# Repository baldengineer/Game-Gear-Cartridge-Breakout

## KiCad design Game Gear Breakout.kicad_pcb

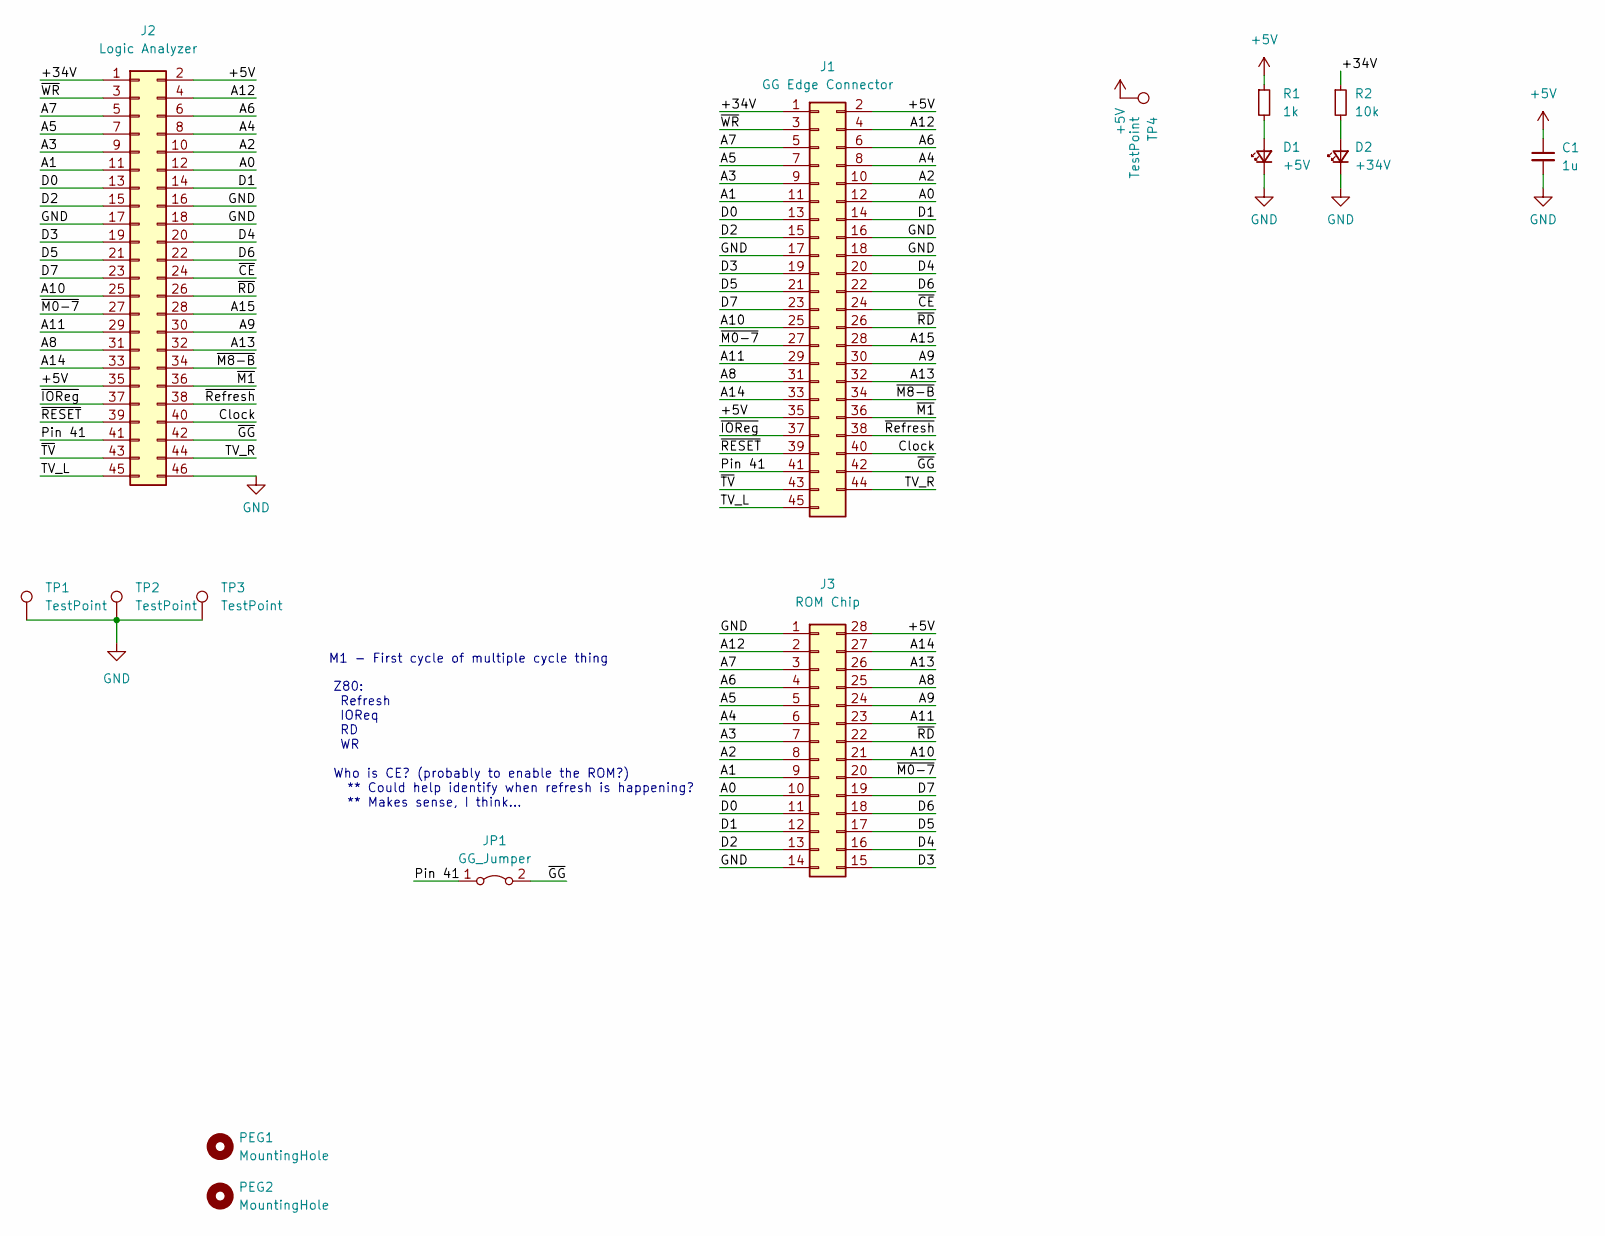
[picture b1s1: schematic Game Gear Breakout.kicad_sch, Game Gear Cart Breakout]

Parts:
C1: 1u; C_0805_2012Metric_Pad1.18x1.45mm_HandSolder
D1: +5V; LED_1206_3216Metric_Pad1.42x1.75mm_HandSolder
D2: +34V; LED_1206_3216Metric_Pad1.42x1.75mm_HandSolder
J1: GG Edge Connector; game gear edge connector
J2: Logic Analyzer; PinHeader_2x23_P2.54mm_Vertical
J3: ROM Chip; SOIC-28W_7.5x17.9mm_P1.27mm
JP1: GG_Jumper; SolderJumper-2_P1.3mm_Bridged_RoundedPad1.0x1.5mm
PEG1, PEG2: MountingHole; MountingHole_2.7mm_M2.5
R1: 1k; R_0805_2012Metric_Pad1.20x1.40mm_HandSolder
R2: 10k; R_0805_2012Metric_Pad1.20x1.40mm_HandSolder
TP1, TP2, TP3, TP4: TestPoint; Harwin-S1751-46-Test-Point

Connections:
+5V: C1.1, J1.2, J1.35, J2.2, J2.35, J3.28, R1.1, TP4.1
/+34V: J1.1, J2.1, R2.1
/A0: J1.12, J2.12, J3.10
/A1: J1.11, J2.11, J3.9
/A2: J1.10, J2.10, J3.8
/A3: J1.9, J2.9, J3.7
/A4: J1.8, J2.8, J3.6
/A5: J1.7, J2.7, J3.5
/A6: J1.6, J2.6, J3.4
/A7: J1.5, J2.5, J3.3
/A8: J1.31, J2.31, J3.25
/A9: J1.30, J2.30, J3.24
/A10: J1.25, J2.25, J3.21
/A11: J1.29, J2.29, J3.23
/A12: J1.4, J2.4, J3.2
/A13: J1.32, J2.32, J3.26
/A14: J1.33, J2.33, J3.27
/A15: J1.28, J2.28
/Clock: J1.40, J2.40
/D0: J1.13, J2.13, J3.11
/D1: J1.14, J2.14, J3.12
/D2: J1.15, J2.15, J3.13
/D3: J1.19, J2.19, J3.15
/D4: J1.20, J2.20, J3.16
/D5: J1.21, J2.21, J3.17
/D6: J1.22, J2.22, J3.18
/D7: J1.23, J2.23, J3.19
/Pin 41: J1.41, J2.41, JP1.1 (A)
/TV_L: J1.45, J2.45
/TV_R: J1.44, J2.44
/~CE: J1.24, J2.24
/~GG: J1.42, J2.42, JP1.2 (B)
/~IOReg: J1.37, J2.37
/~M0-7: J1.27, J2.27, J3.20
/~M1: J1.36, J2.36
/~M8-B: J1.34, J2.34
/~RD: J1.26, J2.26, J3.22
/~RESET: J1.39, J2.39
/~Refresh: J1.38, J2.38
/~TV: J1.43, J2.43
/~WR: J1.3, J2.3
GND: C1.2, D1.1 (K), D2.1 (K), J1.16, J1.17, J1.18, J2.16, J2.17, J2.18, J2.46, J3.1, J3.14, TP1.1, TP2.1, TP3.1
unnamed: D1.2 (A), R1.2
unnamed: D2.2 (A), R2.2

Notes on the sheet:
Z80: Refresh IOReq RD WR Who is CE? (probably to enable the ROM?) ** Could help identify when refresh is happening? ** Makes sense, I think...
M1 - First cycle of multiple cycle thing

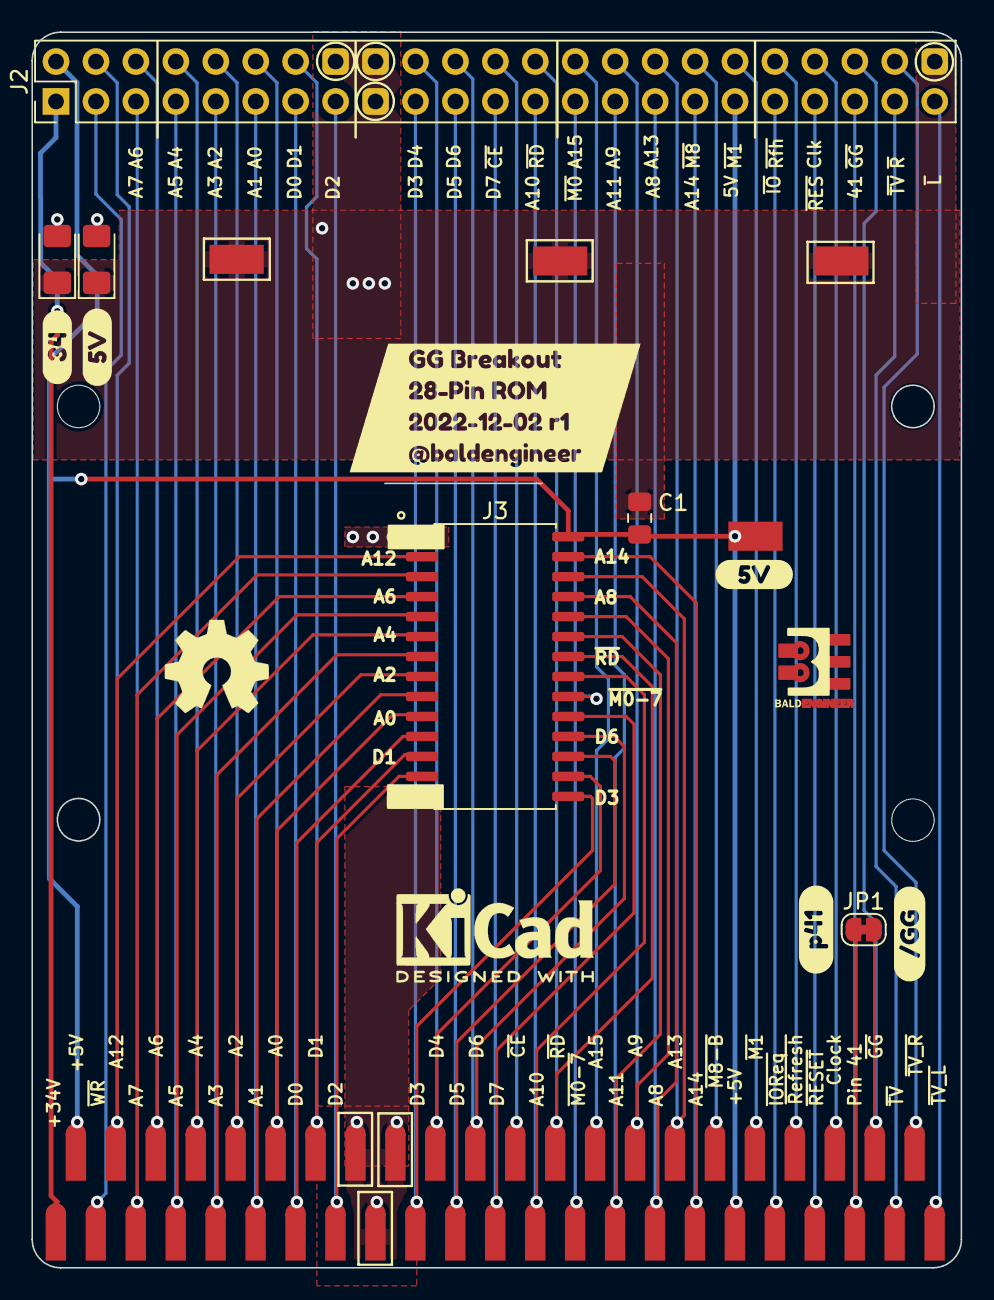
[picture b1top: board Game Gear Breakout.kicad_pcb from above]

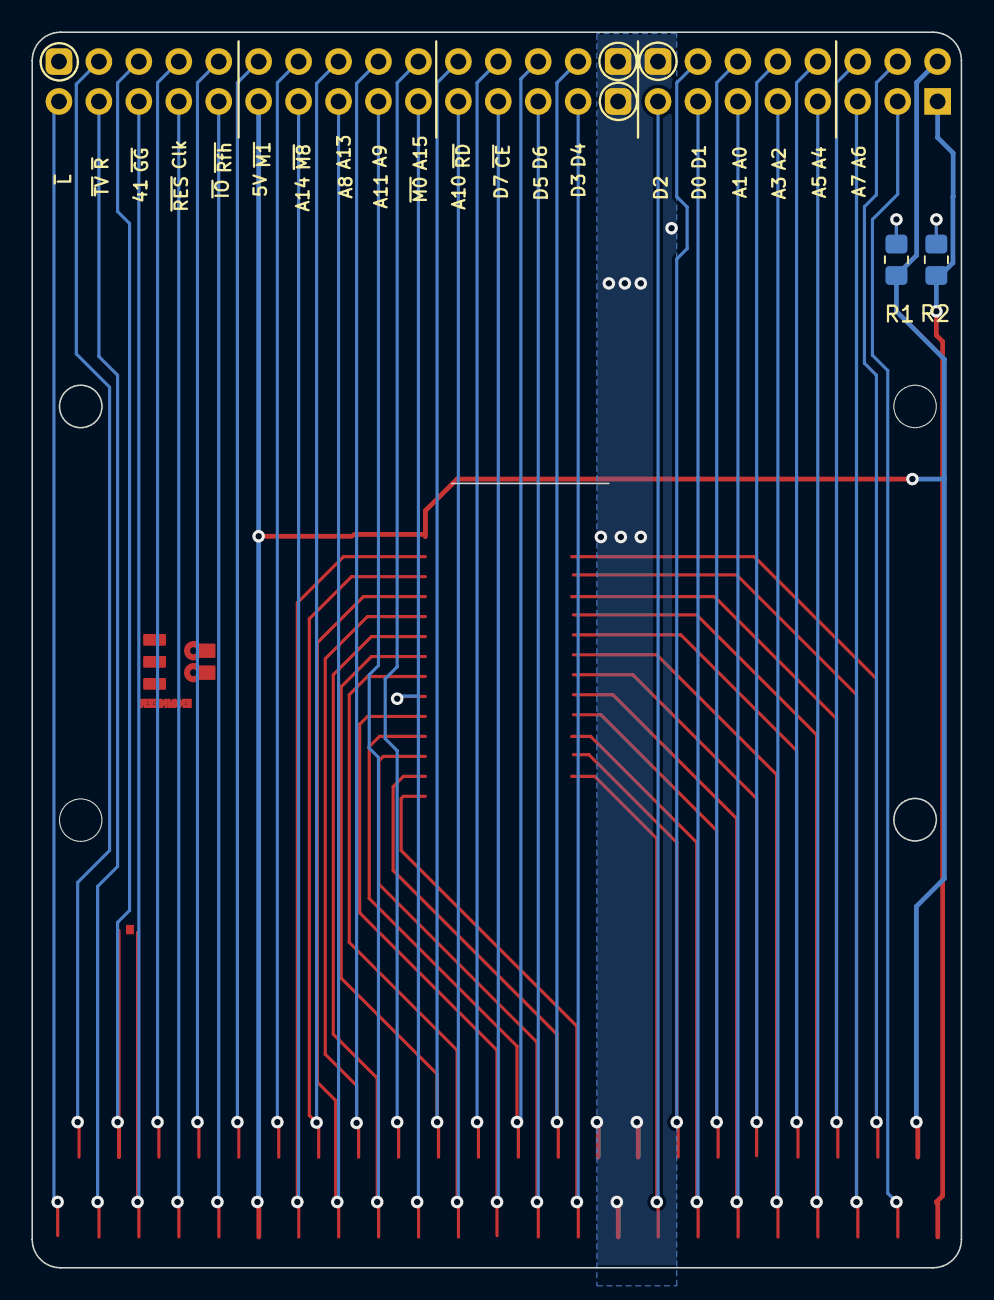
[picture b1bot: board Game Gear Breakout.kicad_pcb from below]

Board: 2 copper layers, 59.1 x 78.6 mm, 22 parts (2 on the bottom side), 44 nets.

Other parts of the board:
kibuzzard-638A45B3, kibuzzard-638A45B3#2: G***; kibuzzard-638A45B3
kibuzzard-638A45BD: G***; kibuzzard-638A45BD
kibuzzard-638A50E1: G***; kibuzzard-638A50E1
kibuzzard-638A474E: G***; kibuzzard-638A474E
kibuzzard-638A4743: G***; kibuzzard-638A4743
svg2mod: G***; BE5v2

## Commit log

2022-12-02 initial
2022-12-02 starting pcb
2022-12-02 added gnd to pin 46 of LA
2022-12-02 DRC rules for PCB
2022-12-02 bottom routed (try #1)
2022-12-02 rev1 layout done?
2022-12-02 v1 submitting to fab
2022-12-02 gerbs and pdf of schematic (v1)
2023-01-09 3d printable shim (so pcb fits in slot)
